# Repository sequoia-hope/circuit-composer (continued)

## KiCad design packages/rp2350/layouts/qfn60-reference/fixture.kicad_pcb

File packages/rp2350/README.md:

# rp2350 0.2.0

A Circuit Composer package for the Raspberry Pi RP2350 family: RP2350A (QFN-60) and RP2350B
(QFN-80). The core voltage regulator has generated, verified layouts for both packages on 2 and 4
layers. The crystal, USB, QSPI flash, buttons and decoupling are intent blocks with cited rules
and with measurements taken from Raspberry Pi's two minimal boards.

| File | What |
|---|---|
| `manifest.toml` | Family, variants and their layouts, source revisions, LCSC parts |
| `intent.json` | The blocks in the intent schema: roles, nets, objectives, constraints, ports. Part names are roles; pins are QFN-60 numbers |
| `ports.json` | Every pin of both variants by number and name, and each function's supply domain, default net class and notes (datasheet §1.2). Its interfaces (I2C0-1, SPI0-1, UART0-1, PWM0-11, SIO, PIO0-2, ADC, USB, SWD, QSPI) and the GPIO function table they reach pins through (`mux`, §1.2.3 Table 3, written by `tools/rp2350_mux.py` from the datasheet) |
| `rules.json` | 27 claims from the datasheet and design guide, each cited, with what enforces it; disputes kept as `contested` |
| `schematic/support.json` | The support parts by block and role as fitted on both minimal boards: value, footprint, designator; decoupling per pin |
| `schematic/circuit.RP2350A.json` | The package's circuit for composing it: 31 parts by role with symbol, value and footprint; 17 internal nets; 37 ports (GND and +3V3 must be connected). Read from the minimal board by `tools/package_circuit.py` |
| `schematic/nets.json` | The package's nets by role pin, and the pin pair each length limit is measured on (`tools/package_nets.py`) |
| `reference/*/` | `ccomp measure` specs and results, and `ccomp check package` bindings and reports, for the two minimal boards |
| `sources/sources.json` | The documents and boards, with SHA-256 hashes |
| `layouts/*/` | Core-regulator layouts and their evidence (below) |

## Variants

The two packages keep the same pin *names*; numbers differ. The regulator's pins 47–50 on QFN-60
are 62–65 on QFN-80, in the same order (PGND, LX, VIN, FB). The QFN-80 adds 18 GPIOs, four of
them ADC inputs, and two more IOVDD pins. To compose a block onto an RP2350B, translate its pins
by name through `ports.json`.

## Core regulator layouts

Each layout folder holds `layout.json` (parts and copper by role, in U1's frame; apply with
`tools/apply_layout.py`), `params.json`, the test bench `fixture.kicad_pcb`/`.kicad_pro`,
`verify.json` (fast-tier measurements and KiCad DRC) and `compare/`, which measures the reference
and the layout with the same checker. `crates/verify/tests/package_layouts.rs` re-measures every
bench on each test run.

| Layout | Bench | Hot loop mm² | Switch node mm² | Output loop mm² | FB clearance mm | Score | Reference score |
|---|---|---|---|---|---|---|---|
| `qfn60-4layer` | easy2350's stack-up | 1.025 | 1.904 | 2.343 | 0.415 | 3.15 | 3.47 (RP2350A Minimal) |
| `qfn60-2layer` | RP2350A Minimal's parts | 1.025 | 1.904 | 2.343 | 0.415 | 3.15 | 3.47 |
| `qfn80-4layer` | RP2350B Minimal's parts, 4 layers | 1.031 | 1.927 | 2.416 | 0.415 | 3.20 | 3.43 (RP2350B Minimal) |
| `qfn80-2layer` | RP2350B Minimal's parts | 1.031 | 1.927 | 2.416 | 0.415 | 3.20 | 3.43 |
| `qfn60-reference` | RP2350A Minimal's parts | 1.064 | 2.349 | 2.452 | 0.365 | 3.46 | 3.47 |
| `qfn80-reference` | RP2350B Minimal's parts | 1.056 | 2.304 | 2.454 | 0.386 | 3.43 | 3.43 |

The two `reference` layouts are Raspberry Pi's own regulator copper, lifted from the minimal
boards by `tools/extract_layout.py`. Each includes the parts' positions, the pours on the
regulator's nets (VIN, LX, core output, the local ground return), and the tracks and vias that
join them, in U1's frame. On their benches they measure what the boards measure. Use one when a
board should carry the vendor's layout rather than the generator's: the pours are what a router
keeps as planes. `apply_layout.py` wraps whatever it places in a KiCad group, `--group NAME`
(`prepare_route.py` passes the rigid block's name). ultraroute treats a group as a block: it
holds the parts still and keeps other nets off the group's pours.

Score = hot loop + 0.5 × switch node + 0.5 × output loop. The QFN-80 comparison also measures
rp2350-motor-controller rev A's regulator (3.39). It matches Raspberry Pi's layout except for a
solid In1 ground under LX, which the datasheet asks to cut away (rule `rp2350.vreg.lx_cutout`).
On 2-layer boards the layer under LX is the bottom ground, kept solid as on both minimal
boards, so the cut-out check does not apply there. The generator draws tracks: LX is 0.2 mm wide
where the references pour a 0.3 mm zone. The checks do not yet price trace resistance.

All four benches are KiCad DRC clean. The one finding, `footprint_type_mismatch` on U1, comes with
the vendor footprint: Raspberry Pi's own boards show it too. The bench reports it as a footprint
note.

## Interface blocks, measured on the minimal boards

`ccomp measure` on both boards (`reference/*/measured.json`):

| | RP2350A Minimal | RP2350B Minimal |
|---|---|---|
| XIN pin → crystal | 10.71 mm | 11.17 mm |
| XOUT pin → 1 k → crystal | 2.97 + 5.54 mm | 2.96 + 5.47 mm |
| USB pin → 27 Ω (DP / DM) | 4.13 / 3.88 mm | 3.97 / 3.72 mm |
| QSPI pin → flash (SCLK, SD0–SD3) | 8.7–16.7 mm | 7.2–17.3 mm |
| Vias on crystal, USB, QSPI | 0 | 0 |
| USB, connector side, track with no ground beside it | 0 mm | 0 mm |
| USB, chip side, same (DP / DM) | 1.11 / 1.76 mm | 0.85 / 1.41 mm |
| QSPI, same | 0.82 mm (QSPI_SS) | 1.3–3.1 mm top + about 6 mm bottom per net |
| Decoupling: worst copper path from a power pin | 4.35 mm | 4.86 mm |

What the measurements found:

- **Shared decoupling.** USB_OTP_VDD and QSPI_IOVDD share one capacitor on both boards. The
  design guide says so and defends it as a space trade-off. ADC_AVDD also shares one with the
  IOVDD pin beside it, which neither document mentions. The datasheet asks for a capacitor on
  each pin. Both claims are kept, linked as contradicting; the package follows the reference
  and says to split them where there is room.
- **The QFN-80 board's second memory.** The optional U204 sits on the bottom directly under the
  flash, and its stubs run on B.Cu. So each QSPI net has about 6 mm of track with no ground
  beside it, and the bottom ground under the top-side QSPI tracks is cut. The QFN-60 board's QSPI
  has ground under every millimetre except 0.8 mm of QSPI_SS.
- **USB return path near the chip.** Where USB leaves the QFN, 0.9–1.8 mm per line runs over cut
  ground on both boards, against the guide's own "solid, uninterrupted" rule. At full speed and
  these lengths it is unlikely to matter. The rule is kept as `contested`.

The length limits in `intent.json` are soft and set at the longer of the two references: what
the vendor achieved, not a datasheet limit. QSPI's unreferenced length is treated the same way:
its ceiling is the QFN-80 board's worst net, 9.22 mm, not zero. The design guide asks QSPI only
for short, direct connections, and that board works with every QSPI net partly on B.Cu. The
crystal and USB keep zero; for USB the guide does ask for unbroken ground.

## Judging a board by role

`ccomp check package BOARD --package packages/rp2350 --binding BINDING.json` judges a board
against this package:
- **Binding:** the board's bindings name which board part plays each package part (`CIN` →
  `C14`) and which variant the chip is.
- **Nets:** it finds the package's nets on the board through `schematic/nets.json`. That file is
  generated by `tools/package_nets.py` from both minimal boards' netlists and lists each net's
  pins by role, in RP2350A numbers. RP2350B pins are translated by name.
- **Wiring:** it compares signal nets pin by pin. A resistor or capacitor fitted the other way
  round is accepted and listed.
- **Judging:** it measures and judges every block constraint, every net length limit (between
  the pin pair the reference was measured on), and every part-value check in `rules.json`. Each
  verdict carries its source.

A value string that names no part number ("12MHz" for the crystal) is reported as
unverifiable, not failed. A package part with no board part bound to it is reported as unbound.

| Board | Hard failures | Soft failures | Notes |
|---|---|---|---|
| RP2350A Minimal (`reference/rp2350a_minimal/check.json`) | 0 | 2 | USB chip side over cut ground |
| RP2350B Minimal (`reference/rp2350b_minimal/check.json`) | 0 | 2 | USB chip side over cut ground; its decoupling caps are not bound (their roles are QFN-60 pins) |
| easy2350 (`boards/easy2350/rp2350.check.json`) | 2 | 6 | USB_DP/DM run 6.1 and 8.5 mm on B.Cu over the +3V3 plane, not ground. QSPI runs 4–6 mm longer than the reference, and SCLK, SD0 and SD3 have 9.9–13 mm over +3V3 |

The BOOTSEL resistor's distance to the flash was 3.0 mm in 0.2.0's first draft. Both reference
boards measure 3.9–4.1 mm, so the soft limit is now 4.1 mm, what the vendor achieves.

## Composing the package into a board

`ccomp compose` builds a board from package instances and the board's own parts
(`reference/rp2350a_minimal/compose.json`). The composition names its nets by port
(`mcu.+3V3`, `mcu.USB_DP`) and by board pin (`J1.3`). The composed circuit reproduces both
boards' netlists net for net:
- the RP2350A minimal board, 55 nets;
- easy2350, 65 nets (`boards/easy2350/compose.json`, checked by `crates/ccomp/tests/compose.rs`).

easy2350 departs from the package in four places, and its composition states each one:
- its RUN resistor and button are wired in the other order, so they are the board's own parts;
- R_XOUT is fitted the other way round;
- with no link resistor, QSPI_SS and FLASH_SS are joined;
- a test point taps DVDD.

The RP2350B circuit is not generated yet. Its reference board's decoupling capacitors have no
roles, because the package's decoupling roles are named by QFN-60 pin.

Not in this release: generators for the interface blocks (milestone 5 places them).

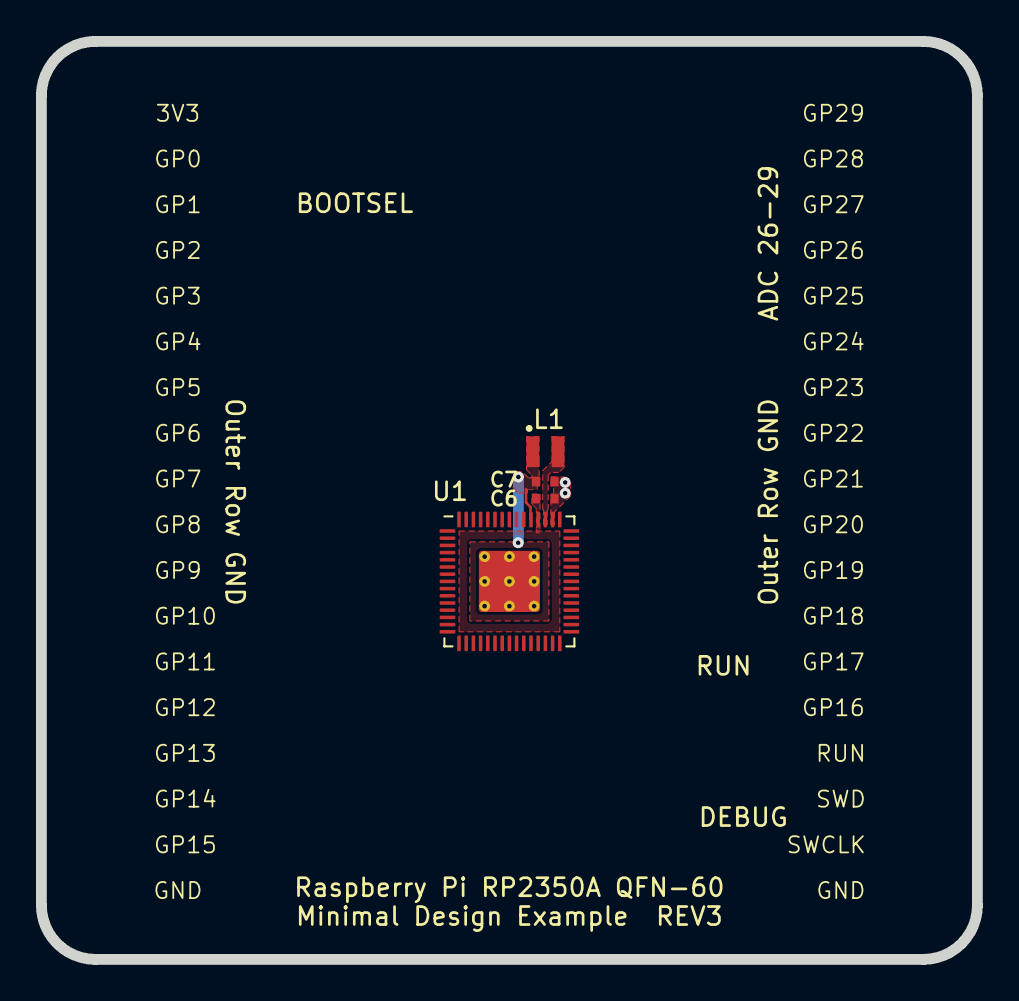
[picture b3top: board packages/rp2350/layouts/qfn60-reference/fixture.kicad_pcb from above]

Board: 2 copper layers, 52.0 x 51.0 mm, 4 parts (0 on the bottom side), 4 nets.

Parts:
C6, C7: 4.7u; C_0402_1005Metric_small_pads
L1: 3.3u; L_pol_2016
U1: RP2350_60QFN; RP2350-QFN-60-1EP_7x7_P0.4mm_EP3.4x3.4mm_ThermalVias

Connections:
+1V1: C7.1, L1.1, U1.6 (DVDD), U1.23 (DVDD), U1.39 (DVDD), U1.50 (VREG_FB)
+3V3: C6.1, U1.1 (IOVDD), U1.11 (IOVDD), U1.20 (IOVDD), U1.30 (IOVDD), U1.38 (IOVDD), U1.44 (ADC_AVDD), U1.45 (IOVDD), U1.49 (VREG_VIN), U1.53 (USB_OTP_VDD), U1.54 (QSPI_IOVDD)
/VREG_LX: L1.2, U1.48 (VREG_LX)
GND: C6.2, C7.2, U1.47 (VREG_PGND), U1.61 (GND)

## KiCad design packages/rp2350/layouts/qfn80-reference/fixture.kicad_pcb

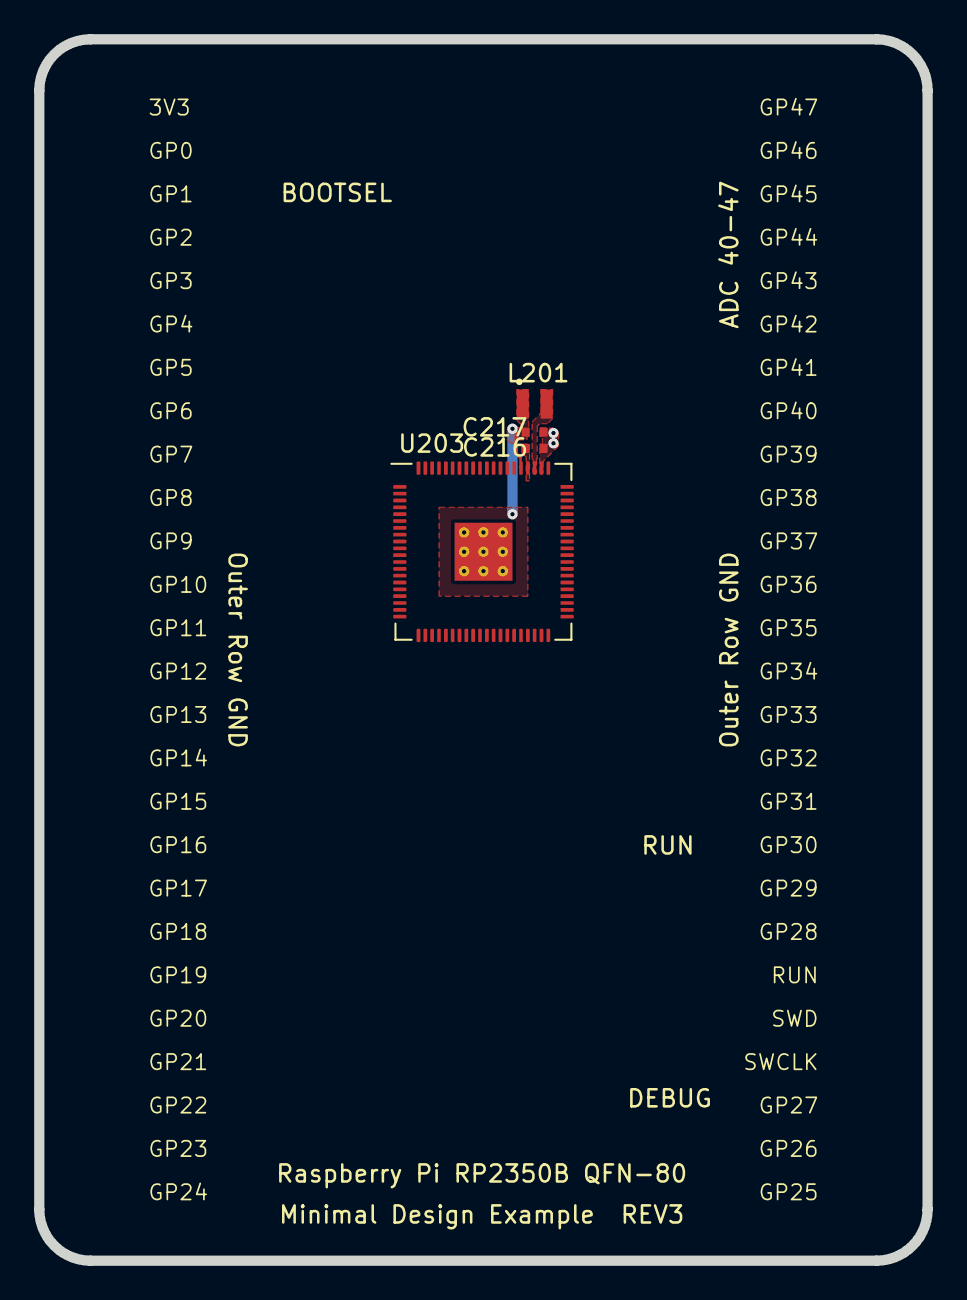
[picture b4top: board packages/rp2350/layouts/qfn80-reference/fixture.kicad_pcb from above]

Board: 2 copper layers, 52.0 x 71.5 mm, 4 parts (0 on the bottom side), 4 nets.

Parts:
C216, C217: 4.7u; C_0402_1005Metric_small_pads
L201: 3.3u; L_pol_2016
U203: RP2350_80QFN; RP2350-QFN-80-1EP_10x10_P0.4mm_EP3.4x3.4mm_ThermalVias

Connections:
+1V1: C217.1, L201.1, U203.10 (DVDD), U203.32 (DVDD), U203.51 (DVDD), U203.65 (VREG_FB)
+3V3: C216.1, U203.5 (IOVDD), U203.15 (IOVDD), U203.24 (IOVDD), U203.29 (IOVDD), U203.41 (IOVDD), U203.50 (IOVDD), U203.59 (ADC_AVDD), U203.60 (IOVDD), U203.64 (VREG_VIN), U203.68 (USB_OTP_VDD), U203.69 (QSPI_IOVDD), U203.76 (IOVDD)
/VREG_LX: L201.2, U203.63 (VREG_LX)
GND: C216.2, C217.2, U203.62 (VREG_PGND), U203.81 (GND)

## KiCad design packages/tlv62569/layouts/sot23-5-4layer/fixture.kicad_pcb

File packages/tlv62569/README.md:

# tlv62569 0.1.0

A Circuit Composer package for the Texas Instruments TLV62569, a 2 A synchronous step-down
converter. It packages the TLV62569DBV (SOT-23-5) in the datasheet's typical application
(SLVSDG1C Figure 5, p.8), set for a 3.3 V rail fed from a 1S LiPo (3.0-4.2 V) or from USB 5 V
(up to 5.5 V). The milestone 5 board needs up to 600 mA from it.

| File | What |
|---|---|
| `manifest.toml` | Variant, source revisions, LCSC parts with stock on 2026-10-27 |
| `ports.json` | The five DBV pins by number, and each function's class, supply and limits (§5 p.3); its one interface, the EN input |
| `rules.json` | 18 claims: 17 from the datasheet, 1 from the inductor's catalogue. 7 of them carry part-value `checks`, and 11 link to 12 claims in `library/claims/buck.json` |
| `schematic/circuit.TLV62569DBV.json` | The circuit: 8 parts by role, nets SW and FB, ports VIN, VOUT, GND (must be connected) and EN |
| `intent.json` | One `buck` block, `reg`, in the shape of rp2350's `core_reg`: roles, nets, objectives, a constraint, ports |
| `sources/sources.json` | Datasheet and inductor catalogue, with SHA-256 hashes |

The DBV variant has **no power-good pin**. PG is only on the TLV62569PDDC (SOT-23-6) and the
TLV62569PDRL (SOT563) (Device Comparison p.1, Pin Functions p.3).

## The circuit and why

| Role | Figure 5 | Value | Part (LCSC) | Why |
|---|---|---|---|---|
| U1 | — | TLV62569DBV | TLV62569DBVR (C141836) | |
| CIN | C1 | 10 uF 25 V X5R 0805 | CL21A106KAYNNNE (C15850) | The datasheet needs at least 4.7 uF and says more reduces ripple (§8.2.2.5 p.10). 10 uF leaves margin for DC-bias loss up to 5.5 V |
| L1 | L1 | 2.2 uH | SXN SMNR4020-2.2UH (C135262) | 2.2 uH is Table 4's standard value (p.9). The part is shielded, DCR 40 mOhm, rated 3.40 A |
| COUT | C2 | 22 uF 25 V X5R 0805 | CL21A226MAQNNNE (C45783) | Table 4 has 2.2 uH + 22 uF as a checked combination. It leaves margin over the 10 uF standard for DC bias at 3.3 V, and lowers the Power Save Mode overshoot (§7.3.1). The datasheet's range is 10-47 uF (§8.2.2.5) |
| RFB_TOP | R1 | 453 k 1 % | C27009 | VOUT = 0.6 × (1 + R1/R2) (Equation 2, p.9). This gives 3.318 V nominal, and 3.25-3.39 V over VFB's 0.588-0.612 V (p.4) |
| RFB_BOT | R2 | 100 k 1 % | C25741 | The datasheet limits R2 to 200 k at most (§8.2.2.2). The CFF value is given for 100 k. The divider draws 6 uA |
| CFF | C3 | 6.8 pF C0G | C1576 | "6.8-pF capacitance is recommended for R2 of 100-kΩ" (§8.2.2.2), for transient response (Figure 19) |
| R_EN | (none) | 1 M | C26083 | Pulls EN up to VIN (see below) |

**Inductor current.** Equation 3 (p.10) at VIN = 5.5 V gives a ripple dIL of
3.3 × (1 − 3.3/5.5) / (2.2 uH × 1.5 MHz) = 0.40 A. At 600 mA the peak IL,MAX is then 0.80 A,
and the datasheet's 20-30 % margin asks for Isat ≥ 1.04 A. At the IC's full 2 A the same sums
give 2.2 A and a 2.86 A requirement. The SMNR4020-2.2UH's 3.40 A rating covers both, and also
the high-side current limit (3 A typical, p.5). The catalogue does not say whether its "Rated DC
Current" is saturation or heating; LCSC lists it as Isat. The Sunlord SWPA4020S2R2MT
(C83423) would be the better-known choice, but LCSC returns no data for it (lifecycle unknown).

**EN: a port, pulled up.** Figure 5 ties EN straight to VIN. The datasheet requires that EN
"must be terminated and should not be left floating" (§7.4.1 p.7). The package therefore adds
R_EN (1 M to VIN) and exposes EN as a signal port:
- A board can leave EN unconnected and the rail is always on.
- It can pull EN below 0.4 V (a slide switch or an open drain) to shut the rail down. That draws
  4.2 uA through R_EN from a full cell, plus the IC's 2 uA maximum shutdown current (p.4).

The datasheet does not specify EN's input current. The 1 M value assumes it is far below 1 uA,
because VIH maximum is only 1.2 V. A board that wants Figure 5 exactly omits R_EN and ties EN
to VIN.

**Low battery: 100 % duty cycle.** As the cell falls toward VOUT, the converter holds its
high-side switch on (§7.3.2 p.6). It keeps regulating down to
VIN(MIN) = VOUT + IOUT × (RDS(on) + DCR) = 3.318 + 0.6 × (0.100 + 0.040) ≈ 3.40 V at 600 mA
(3.41 V with the DCR at its +30 % limit). Below that, VOUT follows the cell about 84 mV under
it. This continues down to the under-voltage lockout, 2.3 V typical and 2.45 V maximum, falling
(p.4). So at a 3.0 V cell the rail is about 2.9 V.

The rp2350 package records VREG_VIN/VREG_AVDD as 3.135-3.63 V. The rail leaves that range
when the cell drops below about 3.22 V at 600 mA, or a little lower at a lighter load. The board
should therefore stop or warn on a battery reading near 3.3 V, not rely on the UVLO.

RDS(on) is a typical value at VIN = 5 V and 25 °C, and the datasheet gives no curve against
VIN. These dropout figures are estimates.

## Rules and library links

The datasheet's layout guidelines (§10.1 p.13) map onto library claims as follows:
- Parts close, power traces short and wide: supports `buck.hot_loop.cin_first_closest`,
  `buck.out_loop.cout_at_inductor` and `buck.sw.min_area`.
- Capacitor grounds to power GND: supports `buck.ground.solid_plane`.
- FB traces away from SW: supports `buck.fb.away_from_sw_and_inductor`.
- GND layers for shielding: supports `buck.fb.shielded_other_layer`.
- Figure 20's DBV layout supports `buck.fb.sense_at_cout` and `buck.fb.divider_at_ic`.

The CIN and COUT rules support `buck.cap.ceramic_low_esr`, and the inductor part supports
`buck.inductor.shielded`.

Three claims refine library claims:
- the Isat margin refines `buck.inductor.isat_above_peak`;
- the -50 % capacitance allowance built into Table 4 refines `buck.cap.dc_bias_effective`;
- the CFF rule refines `buck.fb.divider_at_ic`.

No claim contradicts the library. Figure 20 puts C1's and C2's grounds a few millimetres apart
on one pour, which sits against `buck.ground.cin_cout_separation` (10-20 mm). The datasheet
states no distance, so this is recorded as a note, not a `contradicts` link.

The datasheet gives no feedback clearance in millimetres. The intent's 0.3 mm is the rp2350
floor, borrowed and marked `soft`.

## What is verified, what is not

Verified:
- `python3 tools/circuit_check.py` passes for `schematic/circuit.TLV62569DBV.json`. The
  symbol `Regulator_Switching:TLV62569DBV` (extends TLV62568DBV) has pins EN 1, GND 2, SW 3,
  VIN 4, FB 5, the same as the datasheet p.3.
- `ccomp library check` passes (ok: true).
- All 15 quotes are found on their pages by `tools/library_quotes.py`.
- `ccomp resolve intent.json` parses.

Not verified:
- The inductor footprint is KiCad's `L_Sunlord_SWPA4020S`, not one drawn from the SXN catalogue.
  Its 1.1 × 3.7 mm pads at ±1.5 mm cover SXN's recommended 0.95 × 3.3 mm pads 2.1 mm apart (p.4).
- The capacitors' DC-bias curves were not read, so their effective capacitance at 3.3-5.5 V is
  not quantified.
- Thermal behaviour is unchecked: RθJA is 188.2 °C/W (p.4), and the datasheet has no loss data
  for 3.3 V out from a 3.0-4.2 V input.

## Layout

`layouts/sot23-5-4layer/` is the block as `ccomp gen buck` places it: parts and copper by role in
U1's frame (`layout.json`, applied by `tools/apply_layout.py`), `params.json`, `roles.json`, the
test bench `fixture.kicad_pcb`/`.kicad_pro` (rp2350-battery's U5 and its block, on a 4-layer
board with a solid In1 ground), `verify.json` (the verifier's measurements, KiCad DRC, the
generator's estimate) and `block.svg`. `crates/verify/tests/package_layouts.rs` re-measures the
bench on each test run.

| | Hot loop mm² | Hot loop, pad centres mm² | Output loop mm² | Switch node mm² | FB clearance mm |
|---|---|---|---|---|---|
| Generated, measured | 3.54 | 1.72 | 11.05 | 5.21 | 2.67 |
| Generator's estimate | 3.04 | | 9.81 | 5.92 | 3.52 |
| Free-routed on rp2350-battery (3 placements) | 2.98 to 11.4 | | 12.8 to 16.2 | 5.1 | 0.87 |

How it differs from the RP2350's core regulator, and from TI's DBV example (§10.2 Figure 20 p.13,
`tlv62569.layout.dbv_example`):
- **Ground through the plane** (`gnd_return_vias`). VIN (4) sits across the package from GND (2)
  and SW (3), and GND is beside SW. A same-layer ground run from CIN back to pin 2 would box SW
  in, so the GND pin gets a via just past its pad, CIN's and COUT's ground pads get two each, and
  the loops close on In1 under the parts, as TI's layout does
  (`tlv62569.layout.cap_ground`).
- **The divider** sits by FB: RFB_BOT from FB to a ground via, RFB_TOP from FB to the VOUT sense,
  CFF across RFB_TOP. Every FB run is at least 0.3 mm from switch-node copper
  (`tlv62569.layout.fb_away_from_sw`; the generator's floor, borrowed from the rp2350 package).
  The VOUT sense runs from COUT's pad on F.Cu here. When it does not fit, it is left to the
  router, which TI's example routes on another layer.
- **No switch-node keepout.** This datasheet does not ask for one, and In1 stays solid ground
  under SW (`switch_node_underlap_mm2` is 5.24 and unconstrained here).
- The search reaches 4 mm behind SW's row (`back`), so CIN can sit on VIN's side.

## For the buck generator and checker

`ccomp check buck` takes the output net from the inductor's other pad, and when FB sits behind a
divider it measures the feedback path from the FB pin to the nearest divider pad. The run from
COUT to RFB_TOP is not measured. `ccomp gen buck` takes `rfb_top`, `rfb_bot` and `cff` roles
(above). Regenerate with:

    ~/.claude/bin/reserve -c 8 -l "tlv62569 buck" -- bash -c 'RAYON_NUM_THREADS=$RESERVED_CORES \
      python3 tools/bench_buck.py packages/tlv62569/layouts/sot23-5-4layer/fixture.kicad_pcb \
      packages/tlv62569/layouts/sot23-5-4layer/roles.json OUT --params packages/tlv62569/layouts/sot23-5-4layer/params.json'

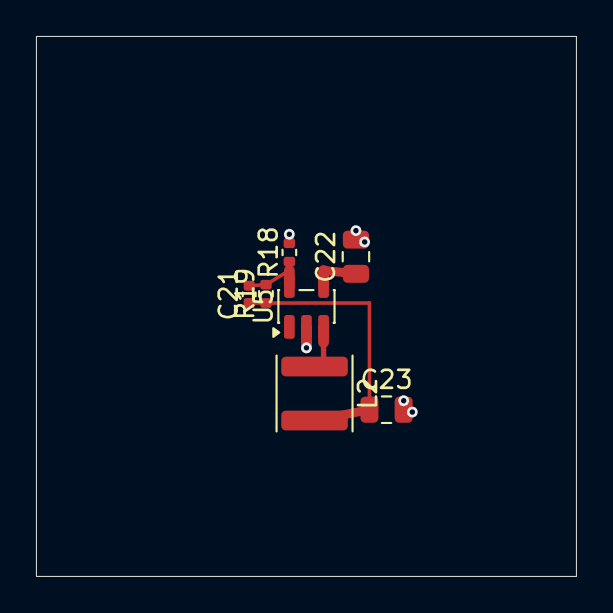
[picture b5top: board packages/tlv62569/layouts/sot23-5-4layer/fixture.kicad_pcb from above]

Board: 4 copper layers, 30.0 x 30.0 mm, 7 parts (0 on the bottom side), 5 nets.

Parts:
C21: 6.8p; C_0402_1005Metric
C22: 10u; C_0805_2012Metric
C23: 22u; C_0805_2012Metric
L2: 2.2u; L_Sunlord_SWPA4020S
R18: 100k; R_0402_1005Metric
R19: 453k; R_0402_1005Metric
U5: TLV62569DBV; SOT-23-5

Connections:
/+3V3: C21.1, C23.1, L2.2, R19.1
/GND: C22.2, C23.2, R18.2, U5.2
/VSYS: C22.1, U5.4
/reg_FB: C21.2, R18.1, R19.2, U5.5
/reg_SW: L2.1, U5.3

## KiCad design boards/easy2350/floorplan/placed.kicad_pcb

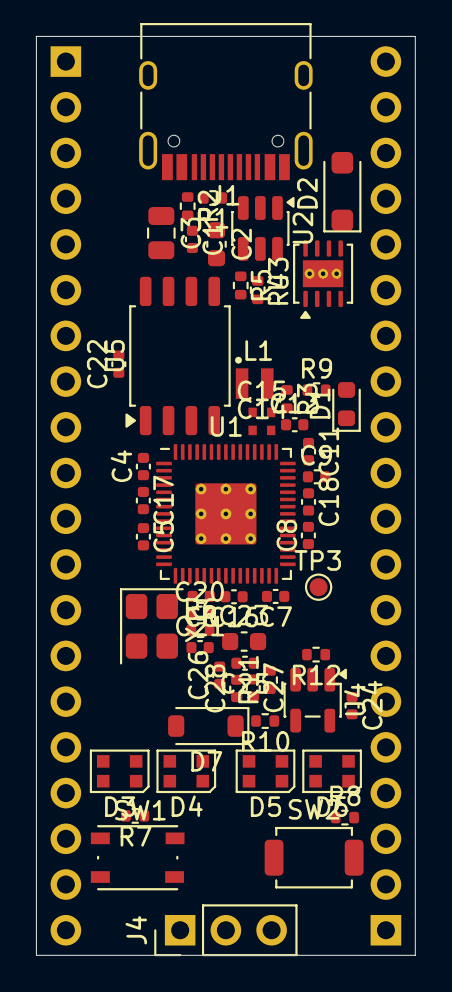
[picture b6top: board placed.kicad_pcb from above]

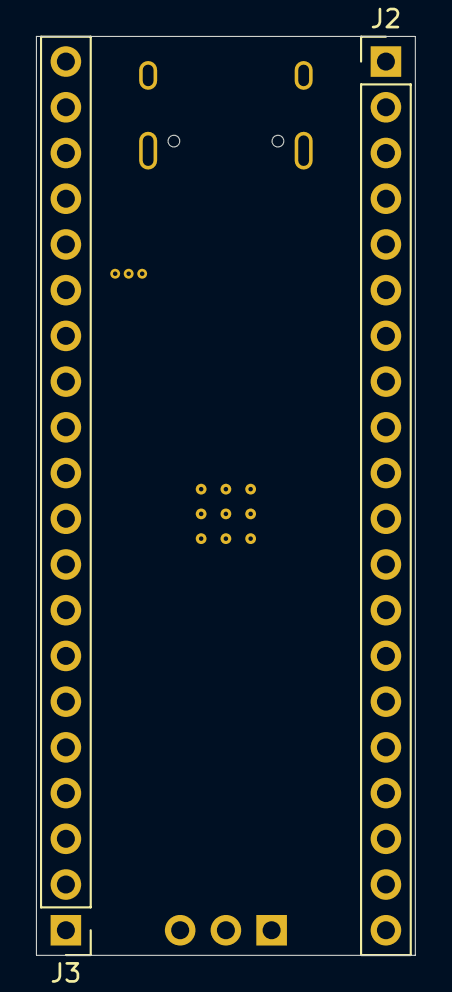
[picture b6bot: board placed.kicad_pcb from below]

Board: 2 copper layers, 21.1 x 51.1 mm, 58 parts (2 on the bottom side), 65 nets, no tracks yet.

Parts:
C1, C4, C5, C6, C7, C8, C9, C11, C17, C18, C22, C24, C25, C26, C27, C28: 100n; C_0402_1005Metric
C2: 2.2u; C_0603_1608Metric
C3: 10u; C_0805_2012Metric
C13, C16: 4.7u; C_0402_1005Metric
C14, C15: 4.7u; C_0402_1005Metric_small_pads
C20, C21: 15p; C_0402_1005Metric
C23: 4.7u; C_0603_1608Metric
D1: RED; LED_0603_1608Metric
D2: SM4007PL; D_SOD-123F_MDD
D3, D4, D5, D6: WS2812B-2020-V6; LED_WS2812B-2020_PLCC4_2.0x2.0mm
D7: BZT52B5V1; D_SOD-123
J1: USB-C; USB_C_Receptacle_HRO_TYPE-C-31-M-12
J2: GPIO left; PinHeader_1x20_P2.54mm_Vertical
J3: GPIO right; PinHeader_1x20_P2.54mm_Vertical
J4: SWD; PinHeader_1x03_P2.54mm_Vertical
L1: 3.3u; L_pol_2016
R1, R2: 5.1k; R_0402_1005Metric
R3: 33; R_0402_1005Metric
R4, R5: 27; R_0402_1005Metric
R6, R7, R8, R9: 1k; R_0402_1005Metric
R10: 33R; R_0402_1005Metric
R11: 4.7k; R_0402_1005Metric
R12: 100k; R_0402_1005Metric
SW1: SW_Push; SW_Push_1P1T_NO_Vertical_Wuerth_434133025816
SW2: RESET; SW_SPST_TS-1088-xR020
TP3: 1V1; TestPoint_Pad_D1.0mm
U1: RP2350_60QFN; RP2350-QFN-60-1EP_7x7_P0.4mm_EP3.4x3.4mm_ThermalVias
U2: USBLC6-2SC6; SOT-23-6
U3: AP7361C-33FGE; DFN-8-1EP_3x3mm_P0.65mm_EP1.5x2.25mm_ThermalVias
U4: SN74LV1T125DBVR; SOT-23-5
U5: W25Q128JVS; SOIC-8_5.3x5.3mm_P1.27mm
Y1: ABM8-272-T3; Crystal_SMD_3225-4Pin_3.2x2.5mm

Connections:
/+1V1: C15.1, C16.1, C17.1, C18.1, L1.1, TP3.1, U1.6, U1.23, U1.39, U1.50
/+3V3: C3.1, C4.1, C5.1, C6.1, C7.1, C8.1, C9.1, C11.1, C14.1, C22.1, J3.16, R3.1, U1.1, U1.11, U1.20, U1.30, U1.38, U1.44, U1.45, U1.49, U1.53, U1.54, U3.1, U5.8
/CC1: J1.A5, R1.1
/CC2: J1.B5, R2.1
/GND: C1.2, C2.2, C3.2, C4.2, C5.2, C6.2, C7.2, C8.2, C9.2, C11.2, C13.2, C14.2, C15.2, C16.2, C17.2, C18.2, C20.2, C21.2, C22.2, C23.2, C24.2, C25.2, C26.2, C27.2, C28.2, D1.1, D3.2, D4.2, D5.2, D6.2, D7.2, J1.A1, J1.A12, J1.B1, J1.B12, J1.S1, J2.3, J2.8, J2.13, J2.18, J3.3, J3.8, J3.18, J4.2, R1.2, R2.2, R11.2, R12.2, SW1.1, SW2.1, U1.47, U1.61, U2.2, U3.4, U3.9, U4.1, U4.3, U5.4, Y1.2, Y1.4
/GPIO0: J2.1, U1.2
/GPIO1: J2.2, U1.3
/GPIO2: J2.4, U1.4
/GPIO3: J2.5, U1.5
/GPIO4: J2.6, U1.7
/GPIO5: J2.7, U1.8
/GPIO6: J2.9, U1.9
/GPIO7: J2.10, U1.10
/GPIO8: J2.11, U1.12
/GPIO9: J2.12, U1.13
/GPIO10: J2.14, U1.14
/GPIO11: J2.15, U1.15
/GPIO12: J2.16, U1.16
/GPIO13: J2.17, U1.17
/GPIO14: J2.19, U1.18
/GPIO15: J2.20, U1.19
/GPIO16: J3.1, U1.27
/GPIO17: J3.2, U1.28
/GPIO18: J3.4, U1.29
/GPIO19: J3.5, U1.31
/GPIO20: J3.6, U1.32
/GPIO21: J3.7, U1.33
/GPIO22: J3.9, U1.34
/GPIO23: J3.11, R12.1, U1.35, U4.2
/GPIO24: J3.12, U1.36
/GPIO25: J3.13, R9.1, U1.37
/GPIO26: J3.14, U1.40
/GPIO27: J3.15, U1.41
/GPIO28: J3.17, U1.42
/GPIO29: J3.19, U1.43
/LED_DIN: D3.3, R10.2
/Net-(D1-A): D1.2, R9.2
/Net-(R8-Pad2): R8.2, SW2.2
/Net-(U4-Y): R10.1, U4.4
/PIX12: D3.1, D4.3
/PIX23: D4.1, D5.3
/PIX34: D5.1, D6.3
/RUN: J3.10, R8.1, U1.26
/SWCLK: J4.1, U1.24
/SWDIO: J4.3, U1.25
/USB_DM: R4.1, U2.6
/USB_DM_C: J1.A7, J1.B7, U2.1
/USB_DP: R5.1, U2.4
/USB_DP_C: J1.A6, J1.B6, U2.3
/VBUS: C1.1, C2.1, D2.2, J1.A4, J1.A9, J1.B4, J1.B9, J3.20, U2.5, U3.5, U3.8
/VLED: C23.1, C24.1, C25.1, C26.1, C27.1, C28.1, D2.1, D3.4, D4.4, D5.4, D6.4, D7.1, R11.1, U4.5
/mcu_QSPI_SCLK: U1.56, U5.6
/mcu_QSPI_SD0: U1.57, U5.5
/mcu_QSPI_SD1: U1.59, U5.2
/mcu_QSPI_SD2: U1.58, U5.3
/mcu_QSPI_SD3: U1.55, U5.7
/mcu_QSPI_SS: R7.1, U1.60, U5.1
/mcu_USB_DM_PIN: R4.2, U1.51
/mcu_USB_DP_PIN: R5.2, U1.52
/mcu_VREG_AVDD: C13.1, R3.2, U1.46
/mcu_VREG_LX: L1.2, U1.48
/mcu_XIN: C20.1, U1.21, Y1.1
/mcu_XOUT: R6.2, U1.22
/mcu_XOUT_XTAL: C21.1, R6.1, Y1.3
/mcu_~USB_BOOT: R7.2, SW1.2
